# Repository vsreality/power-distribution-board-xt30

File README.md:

# PD-XT30-5 v1.0

VSReality Robotics five-port XT30 power distribution board. All five ports share a passive parallel bus; the intended arrangement is one supply and four loads.

## Board

- 18 x 52 mm, 1.6 mm FR4, two copper layers with 70 um (2 oz) copper per side.
- Two 3.2 mm non-plated M3 mounting holes, 42 mm centre-to-centre.
- Five centred XT30UPB connectors, spaced 7 mm apart and numbered 1-5.
- Port 1: XT30UPB-F; ports 2-5: XT30UPB-M. Confirm connector gender against the intended harness.
- Positive copper occupies the left strip when viewed from the front. Ground fills the remaining available area on both layers; mounting keepouts remain copper-free.
- Branding, model name and v1.0 are printed on the back.

| Front | Back |
| --- | --- |
|  |  |

[Angled 3D view](preview-3d-assembled.png)

## Files

Open `xt30-distribution.kicad_pro` in KiCad 9. The PCB, schematic and project-relative connector STEP models are included.

- `production/`: Gerbers, separate PTH/NPTH drills, IPC-D-356 netlist, fabrication instructions and SHA-256 manifest.
- `PD-XT30-5-v1.0-Production.zip`: verified bare-board manufacturing package.
- `fabrication/`: matching fabrication files and drill maps.
- `DESIGN-NOTES.txt`: mechanical, electrical and fabrication details.
- `drc-report.txt`, `erc-report.txt`, `production-verification.txt`: validation results.
- `models/MODEL-SOURCES.txt`: third-party model provenance; no additional license is asserted for those models.

**Design notes:** DRC/ERC checks pass. Current rating and thermal performance have not been validated. No onboard fusing or reverse-polarity protection.

See [DESIGN-NOTES.txt](DESIGN-NOTES.txt) for detailed validation and rebuild instructions.

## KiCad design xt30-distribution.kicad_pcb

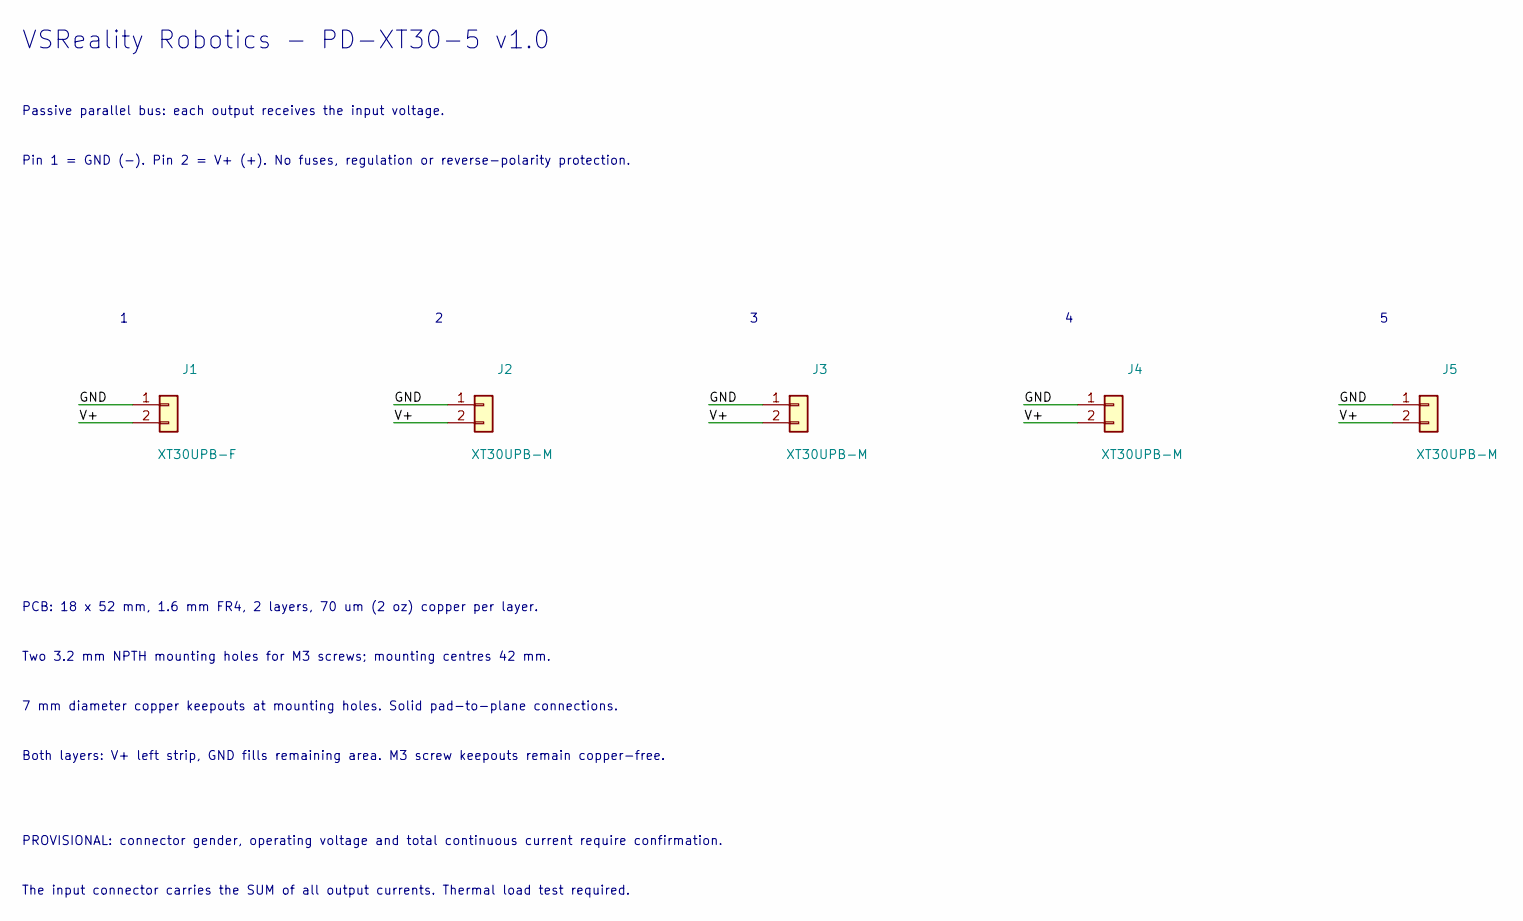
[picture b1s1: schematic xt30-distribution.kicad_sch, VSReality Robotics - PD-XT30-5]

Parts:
J1: XT30UPB-F; AMASS_XT30UPB-F_1x02_P5.0mm_Vertical
J2, J3, J4, J5: XT30UPB-M; AMASS_XT30UPB-M_1x02_P5.0mm_Vertical

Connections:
/GND: J1.1, J2.1, J3.1, J4.1, J5.1
/V+: J1.2, J2.2, J3.2, J4.2, J5.2

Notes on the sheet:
VSReality Robotics - PD-XT30-5 v1.0
Passive parallel bus: each output receives the input voltage.
Pin 1 = GND (-). Pin 2 = V+ (+). No fuses, regulation or reverse-polarity protection.
PCB: 18 x 52 mm, 1.6 mm FR4, 2 layers, 70 um (2 oz) copper per layer.
Two 3.2 mm NPTH mounting holes for M3 screws; mounting centres 42 mm.
7 mm diameter copper keepouts at mounting holes. Solid pad-to-plane connections.
Both layers: V+ left strip, GND fills remaining area. M3 screw keepouts remain copper-free.
PROVISIONAL: connector gender, operating voltage and total continuous current require confirmation.
The input connector carries the SUM of all output currents. Thermal load test required.

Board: 2 copper layers, 7 parts (0 on the bottom side), 2 nets, no tracks yet.

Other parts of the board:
H1, H2: M3 / 3.2mm; MountingHole_3.2mm_M3
